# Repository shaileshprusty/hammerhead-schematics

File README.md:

# hammerhead-schematics
This is the official repository for the Circuit schematics of Hammer-Head (Autonomous Underwater Vehicle of NITR).

### Prerequisites
- [Autodesk Eagle](https://www.autodesk.com/products/eagle/overview)

#### Note
This repository is still under development

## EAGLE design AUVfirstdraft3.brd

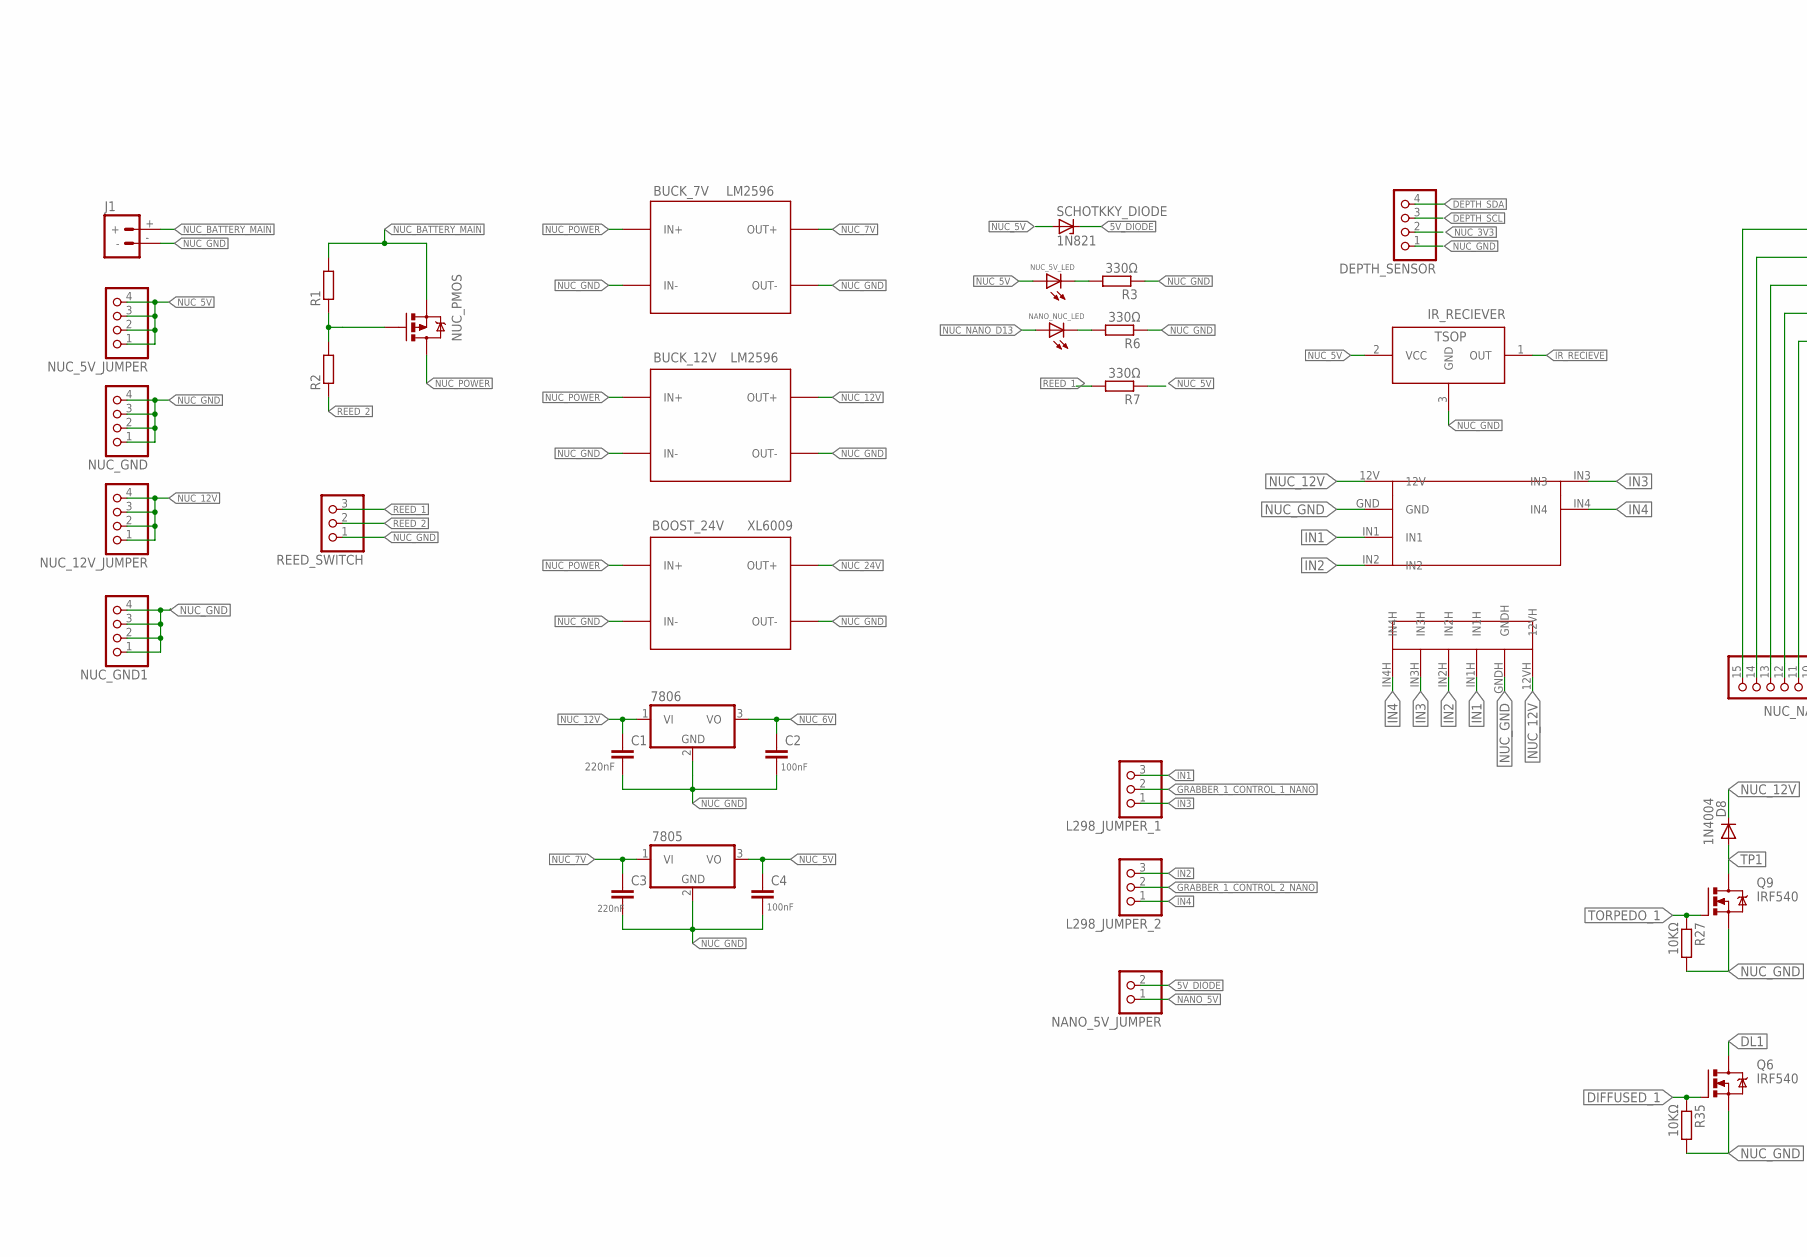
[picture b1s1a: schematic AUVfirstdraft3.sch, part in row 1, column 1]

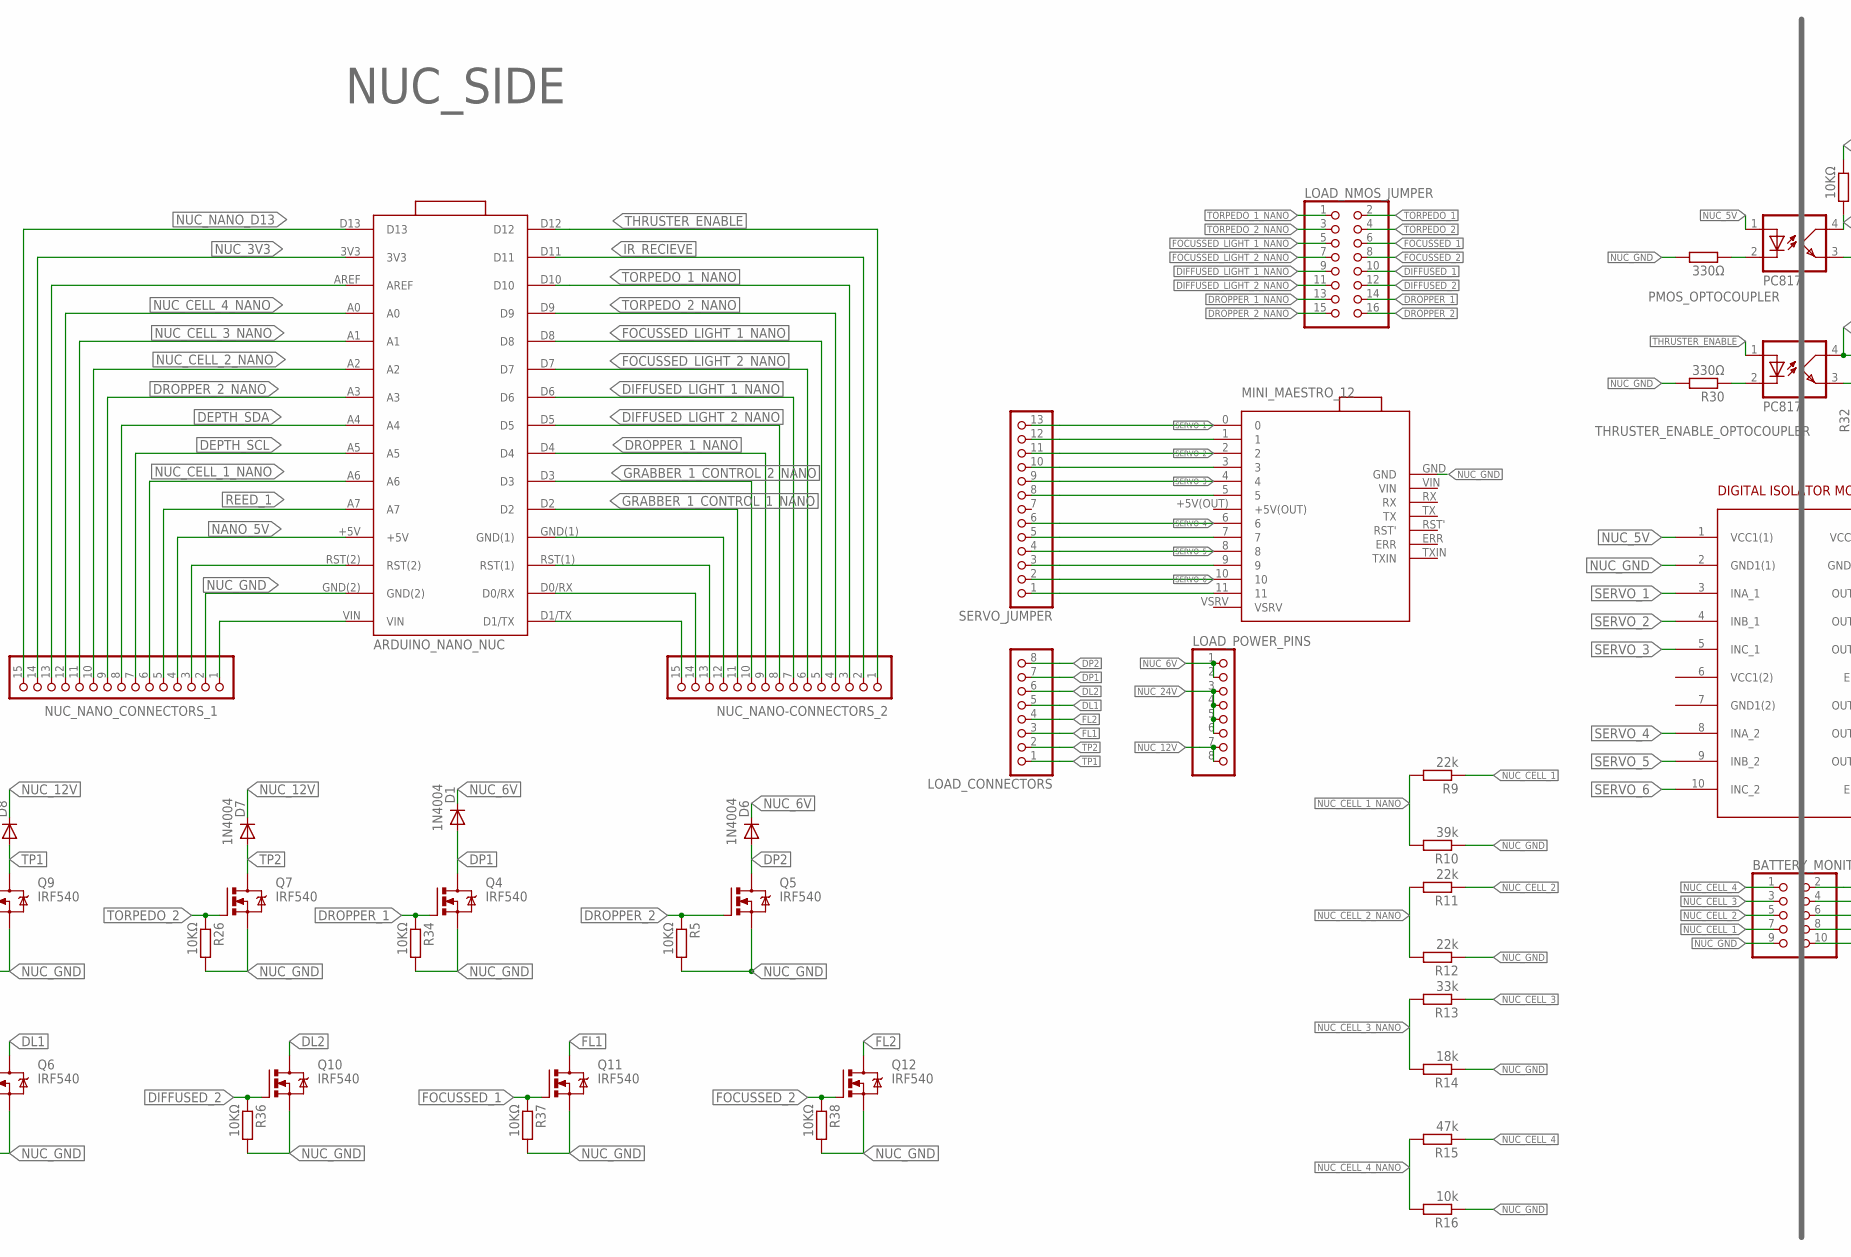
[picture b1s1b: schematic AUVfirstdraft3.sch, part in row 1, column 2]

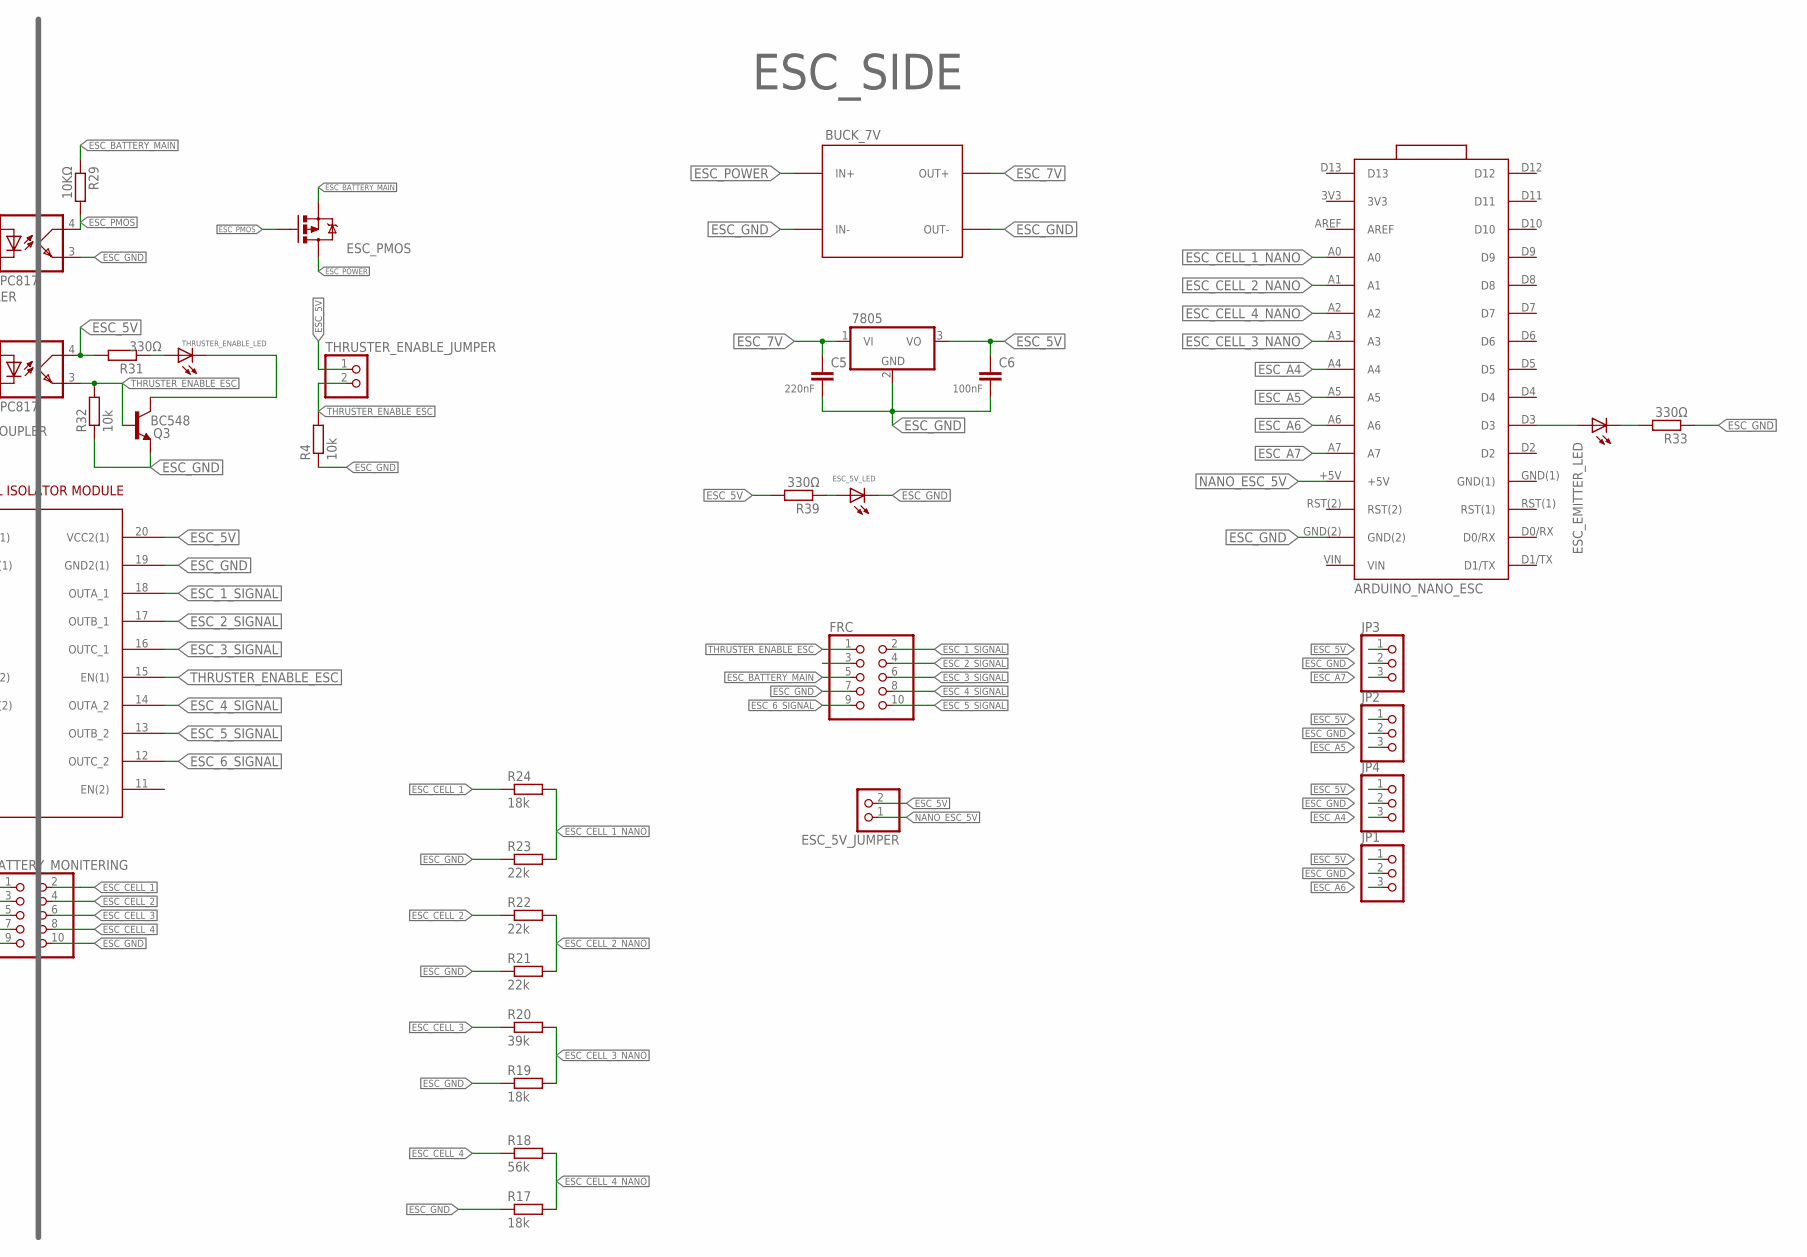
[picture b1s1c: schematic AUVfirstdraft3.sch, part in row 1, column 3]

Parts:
330Ω: R-EU_0204/7; 0204/7
7805_ESC, 7805_NUC, 7806_NUC: 7805TV; TO220V
BATTERY_MONITERING: PINHD-2X5; 2X05
BOOST_24V_NUC: DC-DC-STEP-DOWN-LM2596
BUCK_7V_ESC, BUCK_7V_NUC, BUCK_12_NUC: DC-DC-STEP-DOWN-LM2596
C1, C3, C5: 220nF; C025-024X044
C2, C4, C6: 100nF; C025-024X044
D1, D6, D7, D8: 1N4004; DO41-10
DEPTH_SENSOR: PINHD-1X4; 1X04
ESC_5V_JUMPER: PINHD-1X2; 1X02
ESC_5V_LED: LED3MM
ESC_EMITTER_LED: LED5MM
ESC_PMOS: MOSFET-PCHANNELFQP27P06; TO220V
FRC: PINHD-2X5; 2X05
IR_RECIEVER: TSOP34X; TSOP3XXX
ISOLATION_CIRCUIT: DIGITAL_ISOLATOR; DIGITAL_ISOLATOR_MODULE
J1: BATTERY_CONN_DEANS; DEANS
JP1, JP2, JP3, JP4: PINHD-1X3; 1X03
L298_JUMPER_1, L298_JUMPER_2: PINHD-1X3; 1X03
L298_MOTOR_DRIVER: L298MODULE
LOAD_CONNECTORS: PINHD-1X8; 1X08
LOAD_NMOS_JUMPER: PINHD-2X8; 2X08
LOAD_POWER_PINS: PINHD-1X8; 1X08
NANO_5V_JUMPER: PINHD-1X2; 1X02
NANO_NUC_LED: LED3MM
NUC_5V_JUMPER, NUC_12V_JUMPER: PINHD-1X4; 1X04
NUC_5V_LED: LED3MM
NUC_GND, NUC_GND1: PINHD-1X4; 1X04
NUC_NANO-CONNECTORS_2: PINHD-1X15; 1X15
NUC_NANO_CONNECTORS_1: PINHD-1X15; 1X15
NUC_PMOS: MOSFET-PCHANNELFQP27P06; TO220V
PMOS_OPTOCOUPLER: PC817; DIL04
Q3: BC548; TO92-EBC
Q4, Q5, Q6, Q7, Q9, Q10, Q11, Q12: IRF540; TO220BV
R1, R2: R-EU_0204/7; 0204/7
R3, R6, R7, R30, R31, R33, R39: 330Ω; 0204/7
R4, R16, R32: 10k; 0204/7
R5, R26, R27, R29, R34, R35, R36, R37, R38: 10KΩ; 0204/7
R9, R11, R12, R21, R22, R23: 22k; 0204/7
R10, R20: 39k; 0204/7
R13: 33k; 0204/7
R14, R17, R19, R24: 18k; 0204/7
R15: 47k; 0204/7
R18: 56k; 0204/7
REED_SWITCH: PINHD-1X3; 1X03
SCHOTKKY_DIODE: 1N821; DO35Z10
SERVO_JUMPER: PINHD-1X13; 1X13
THRUSTER_ENABLE_JUMPER: PINHD-1X2; 1X02
THRUSTER_ENABLE_LED: LED3MM
THRUSTER_ENABLE_OPTOCOUPLER: PC817; DIL04
U$1, U$6: ARDUINO(NANO_3.0); ARDUINO_NANO_30PIN
U$4: SERVO_CONTROLLER

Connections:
5V_DIODE: NANO_5V_JUMPER.2, SCHOTKKY_DIODE.C
DEPTH_SCL: DEPTH_SENSOR.3, NUC_NANO_CONNECTORS_1.7, U$1.A5
DEPTH_SDA: DEPTH_SENSOR.4, NUC_NANO_CONNECTORS_1.8, U$1.A4
DIFFUSED_1: LOAD_NMOS_JUMPER.10, Q6.G, R35.1
DIFFUSED_2: LOAD_NMOS_JUMPER.12, Q10.G, R36.1
DIFFUSED_LIGHT_1_NANO: LOAD_NMOS_JUMPER.9, NUC_NANO-CONNECTORS_2.7, U$1.D6
DIFFUSED_LIGHT_2_NANO: LOAD_NMOS_JUMPER.11, NUC_NANO-CONNECTORS_2.8, U$1.D5
DL1: LOAD_CONNECTORS.5, Q6.D
DL2: LOAD_CONNECTORS.6, Q10.D
DP1: D1.A, LOAD_CONNECTORS.7, Q4.D
DP2: D6.A, LOAD_CONNECTORS.8, Q5.D
DROPPER_1: LOAD_NMOS_JUMPER.14, Q4.G, R34.1
DROPPER_1_NANO: LOAD_NMOS_JUMPER.13, NUC_NANO-CONNECTORS_2.9, U$1.D4
DROPPER_2: LOAD_NMOS_JUMPER.16, Q5.G, R5.1
DROPPER_2_NANO: LOAD_NMOS_JUMPER.15, NUC_NANO_CONNECTORS_1.9, U$1.A3
ESC_1_SIGNAL: FRC.2, ISOLATION_CIRCUIT.18 (OUTA_1)
ESC_2_SIGNAL: FRC.4, ISOLATION_CIRCUIT.17 (OUTB_1)
ESC_3_SIGNAL: FRC.6, ISOLATION_CIRCUIT.16 (OUTC_1)
ESC_4_SIGNAL: FRC.8, ISOLATION_CIRCUIT.14 (OUTA_2)
ESC_5V: 7805_ESC.3 (VO), C6.1, ESC_5V_JUMPER.2, ISOLATION_CIRCUIT.20 (VCC2(1)), JP1.1, JP2.1, JP3.1, JP4.1, R31.2, R39.2, THRUSTER_ENABLE_JUMPER.1, THRUSTER_ENABLE_OPTOCOUPLER.4 (COL)
ESC_5_SIGNAL: FRC.10, ISOLATION_CIRCUIT.13 (OUTB_2)
ESC_6_SIGNAL: FRC.9, ISOLATION_CIRCUIT.12 (OUTC_2)
ESC_7V: 7805_ESC.1 (VI), BUCK_7V_ESC.OUT+, C5.1
ESC_A4: JP4.3, U$6.A4
ESC_A5: JP2.3, U$6.A5
ESC_A6: JP1.3, U$6.A6
ESC_A7: JP3.3, U$6.A7
ESC_BATTERY_MAIN: ESC_PMOS.3 (S), FRC.5, R29.1
ESC_CELL_1: BATTERY_MONITERING.2, R24.1
ESC_CELL_1_NANO: R23.2, R24.2, U$6.A0
ESC_CELL_2: BATTERY_MONITERING.4, R22.1
ESC_CELL_2_NANO: R21.2, R22.2, U$6.A1
ESC_CELL_3: BATTERY_MONITERING.6, R20.1
ESC_CELL_3_NANO: R19.2, R20.2, U$6.A3
ESC_CELL_4: BATTERY_MONITERING.8, R18.1
ESC_CELL_4_NANO: R17.2, R18.2, U$6.A2
ESC_GND: 7805_ESC.2 (GND), BATTERY_MONITERING.10, BUCK_7V_ESC.IN-, BUCK_7V_ESC.OUT-, C5.2, C6.2, ESC_5V_LED.K (C), FRC.7, ISOLATION_CIRCUIT.19 (GND2(1)), JP1.2, JP2.2, JP3.2, JP4.2, PMOS_OPTOCOUPLER.3 (EMIT), Q3.E, R4.1, R17.1, R19.1, R21.1, R23.1, R32.1, R33.1, U$6.GND(2)
ESC_PMOS: ESC_PMOS.1 (G), PMOS_OPTOCOUPLER.4 (COL), R29.2
ESC_POWER: BUCK_7V_ESC.IN+, ESC_PMOS.2 (D)
FL1: LOAD_CONNECTORS.3, Q11.D
FL2: LOAD_CONNECTORS.4, Q12.D
FOCUSSED_1: LOAD_NMOS_JUMPER.6, Q11.G, R37.1
FOCUSSED_2: LOAD_NMOS_JUMPER.8, Q12.G, R38.1
FOCUSSED_LIGHT_1_NANO: LOAD_NMOS_JUMPER.5, NUC_NANO-CONNECTORS_2.5, U$1.D8
FOCUSSED_LIGHT_2_NANO: LOAD_NMOS_JUMPER.7, NUC_NANO-CONNECTORS_2.6, U$1.D7
GRABBER_1_CONTROL_1_NANO: L298_JUMPER_1.2, NUC_NANO-CONNECTORS_2.11, U$1.D2
GRABBER_1_CONTROL_2_NANO: L298_JUMPER_2.2, NUC_NANO-CONNECTORS_2.10, U$1.D3
IN1: L298_JUMPER_1.3, L298_MOTOR_DRIVER.IN1, L298_MOTOR_DRIVER.IN1H
IN2: L298_JUMPER_2.3, L298_MOTOR_DRIVER.IN2, L298_MOTOR_DRIVER.IN2H
IN3: L298_JUMPER_1.1, L298_MOTOR_DRIVER.IN3, L298_MOTOR_DRIVER.IN3H
IN4: L298_JUMPER_2.1, L298_MOTOR_DRIVER.IN4, L298_MOTOR_DRIVER.IN4H
IR_RECIEVE: IR_RECIEVER.1 (OUT), NUC_NANO-CONNECTORS_2.2, U$1.D11
unnamed: NUC_NANO_CONNECTORS_1.1, U$1.VIN
unnamed: NANO_NUC_LED.K (C), R6.2
unnamed: R31.1, THRUSTER_ENABLE_LED.A
unnamed: ESC_5V_LED.A, R39.1
unnamed: SERVO_JUMPER.12, U$4.1
unnamed: NUC_NANO_CONNECTORS_1.3, U$1.RST(2)
unnamed: 330Ω.1, PMOS_OPTOCOUPLER.2 (C)
unnamed: SERVO_JUMPER.10, U$4.3
unnamed: ESC_EMITTER_LED.A, U$6.D3
unnamed: SERVO_JUMPER.8, U$4.5
unnamed: SERVO_JUMPER.5, U$4.7
unnamed: R30.1, THRUSTER_ENABLE_OPTOCOUPLER.2 (C)
unnamed: SERVO_JUMPER.3, U$4.9
unnamed: Q3.C, THRUSTER_ENABLE_LED.K (C)
unnamed: NUC_NANO_CONNECTORS_1.13, U$1.AREF
unnamed: ESC_EMITTER_LED.K (C), R33.2
unnamed: SERVO_JUMPER.1, U$4.11
unnamed: NUC_NANO-CONNECTORS_2.15, U$1.D1/TX
unnamed: NUC_NANO-CONNECTORS_2.14, U$1.D0/RX
unnamed: NUC_NANO-CONNECTORS_2.13, U$1.RST(1)
unnamed: NUC_NANO-CONNECTORS_2.12, U$1.GND(1)
unnamed: NUC_PMOS.1 (G), R1.1, R2.2
unnamed: NUC_5V_LED.K (C), R3.2
NANO_5V: NANO_5V_JUMPER.1, NUC_NANO_CONNECTORS_1.4, U$1.+5V
NANO_ESC_5V: ESC_5V_JUMPER.1, U$6.+5V
NUC_3V3: DEPTH_SENSOR.2, NUC_NANO_CONNECTORS_1.14, U$1.3V3
NUC_5V: 7805_NUC.3 (VO), C4.1, IR_RECIEVER.2 (VCC), ISOLATION_CIRCUIT.1 (VCC1(1)), NUC_5V_JUMPER.1, NUC_5V_JUMPER.2, NUC_5V_JUMPER.3, NUC_5V_JUMPER.4, NUC_5V_LED.A, PMOS_OPTOCOUPLER.1 (A), R7.1, SCHOTKKY_DIODE.A
NUC_6V: 7806_NUC.3 (VO), C2.1, D1.C, D6.C, LOAD_POWER_PINS.1, LOAD_POWER_PINS.2
NUC_7V: 7805_NUC.1 (VI), BUCK_7V_NUC.OUT+, C3.1
NUC_12V: 7806_NUC.1 (VI), BUCK_12_NUC.OUT+, C1.1, D7.C, D8.C, L298_MOTOR_DRIVER.12V, L298_MOTOR_DRIVER.12VH, LOAD_POWER_PINS.7, LOAD_POWER_PINS.8, NUC_12V_JUMPER.1, NUC_12V_JUMPER.2, NUC_12V_JUMPER.3, NUC_12V_JUMPER.4
NUC_24V: BOOST_24V_NUC.OUT+, LOAD_POWER_PINS.3, LOAD_POWER_PINS.4, LOAD_POWER_PINS.5, LOAD_POWER_PINS.6
NUC_BATTERY_MAIN: J1.+, NUC_PMOS.3 (S), R1.2
NUC_CELL_1: BATTERY_MONITERING.7, R9.1
NUC_CELL_1_NANO: NUC_NANO_CONNECTORS_1.6, R9.2, R10.2, U$1.A6
NUC_CELL_2: BATTERY_MONITERING.5, R11.1
NUC_CELL_2_NANO: NUC_NANO_CONNECTORS_1.10, R11.2, R12.2, U$1.A2
NUC_CELL_3: BATTERY_MONITERING.3, R13.1
NUC_CELL_3_NANO: NUC_NANO_CONNECTORS_1.11, R13.2, R14.2, U$1.A1
NUC_CELL_4: BATTERY_MONITERING.1, R15.1
NUC_CELL_4_NANO: NUC_NANO_CONNECTORS_1.12, R15.2, R16.2, U$1.A0
NUC_GND: 330Ω.2, 7805_NUC.2 (GND), 7806_NUC.2 (GND), BATTERY_MONITERING.9, BOOST_24V_NUC.IN-, BOOST_24V_NUC.OUT-, BUCK_7V_NUC.IN-, BUCK_7V_NUC.OUT-, BUCK_12_NUC.IN-, BUCK_12_NUC.OUT-, C1.2, C2.2, C3.2, C4.2, DEPTH_SENSOR.1, IR_RECIEVER.3 (GND), ISOLATION_CIRCUIT.2 (GND1(1)), J1.-, L298_MOTOR_DRIVER.GND, L298_MOTOR_DRIVER.GNDH, NUC_GND.1, NUC_GND.2, NUC_GND.3, NUC_GND.4, NUC_GND1.1, NUC_GND1.2, NUC_GND1.3, NUC_GND1.4, NUC_NANO_CONNECTORS_1.2, Q4.S, Q5.S, Q6.S, Q7.S, Q9.S, Q10.S, Q11.S, Q12.S, R3.1, R5.2, R6.1, R10.1, R12.1, R14.1, R16.1, R26.2, R27.2, R30.2, R34.2, R35.2, R36.2, R37.2, R38.2, REED_SWITCH.1, U$1.GND(2), U$4.GND
NUC_NANO_D13: NANO_NUC_LED.A, NUC_NANO_CONNECTORS_1.15, U$1.D13
NUC_POWER: BOOST_24V_NUC.IN+, BUCK_7V_NUC.IN+, BUCK_12_NUC.IN+, NUC_PMOS.2 (D)
REED_1: NUC_NANO_CONNECTORS_1.5, R7.2, REED_SWITCH.3, U$1.A7
REED_2: R2.1, REED_SWITCH.2
SERVO_1: ISOLATION_CIRCUIT.3 (INA_1), SERVO_JUMPER.13, U$4.0
SERVO_2: ISOLATION_CIRCUIT.4 (INB_1), SERVO_JUMPER.11, U$4.2
SERVO_3: ISOLATION_CIRCUIT.5 (INC_1), SERVO_JUMPER.9, U$4.4
SERVO_4: ISOLATION_CIRCUIT.8 (INA_2), SERVO_JUMPER.6, U$4.6
SERVO_5: ISOLATION_CIRCUIT.9 (INB_2), SERVO_JUMPER.4, U$4.8
SERVO_6: ISOLATION_CIRCUIT.10 (INC_2), SERVO_JUMPER.2, U$4.10
THRUSTER_ENABLE: NUC_NANO-CONNECTORS_2.1, THRUSTER_ENABLE_OPTOCOUPLER.1 (A), U$1.D12
THRUSTER_ENABLE_ESC: FRC.1, ISOLATION_CIRCUIT.15 (EN(1)), Q3.B, R4.2, R32.2, THRUSTER_ENABLE_JUMPER.2, THRUSTER_ENABLE_OPTOCOUPLER.3 (EMIT)
TORPEDO_1: LOAD_NMOS_JUMPER.2, Q9.G, R27.1
TORPEDO_1_NANO: LOAD_NMOS_JUMPER.1, NUC_NANO-CONNECTORS_2.3, U$1.D10
TORPEDO_2: LOAD_NMOS_JUMPER.4, Q7.G, R26.1
TORPEDO_2_NANO: LOAD_NMOS_JUMPER.3, NUC_NANO-CONNECTORS_2.4, U$1.D9
TP1: D8.A, LOAD_CONNECTORS.1, Q9.D
TP2: D7.A, LOAD_CONNECTORS.2, Q7.D

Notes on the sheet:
BUCK_7V
BUCK_12V
BOOST_24V
7805
7806
NUC_SIDE
ESC_SIDE
MINI_MAESTRO_12
ARDUINO_NANO_NUC
ARDUINO_NANO_ESC
LM2596
XL6009

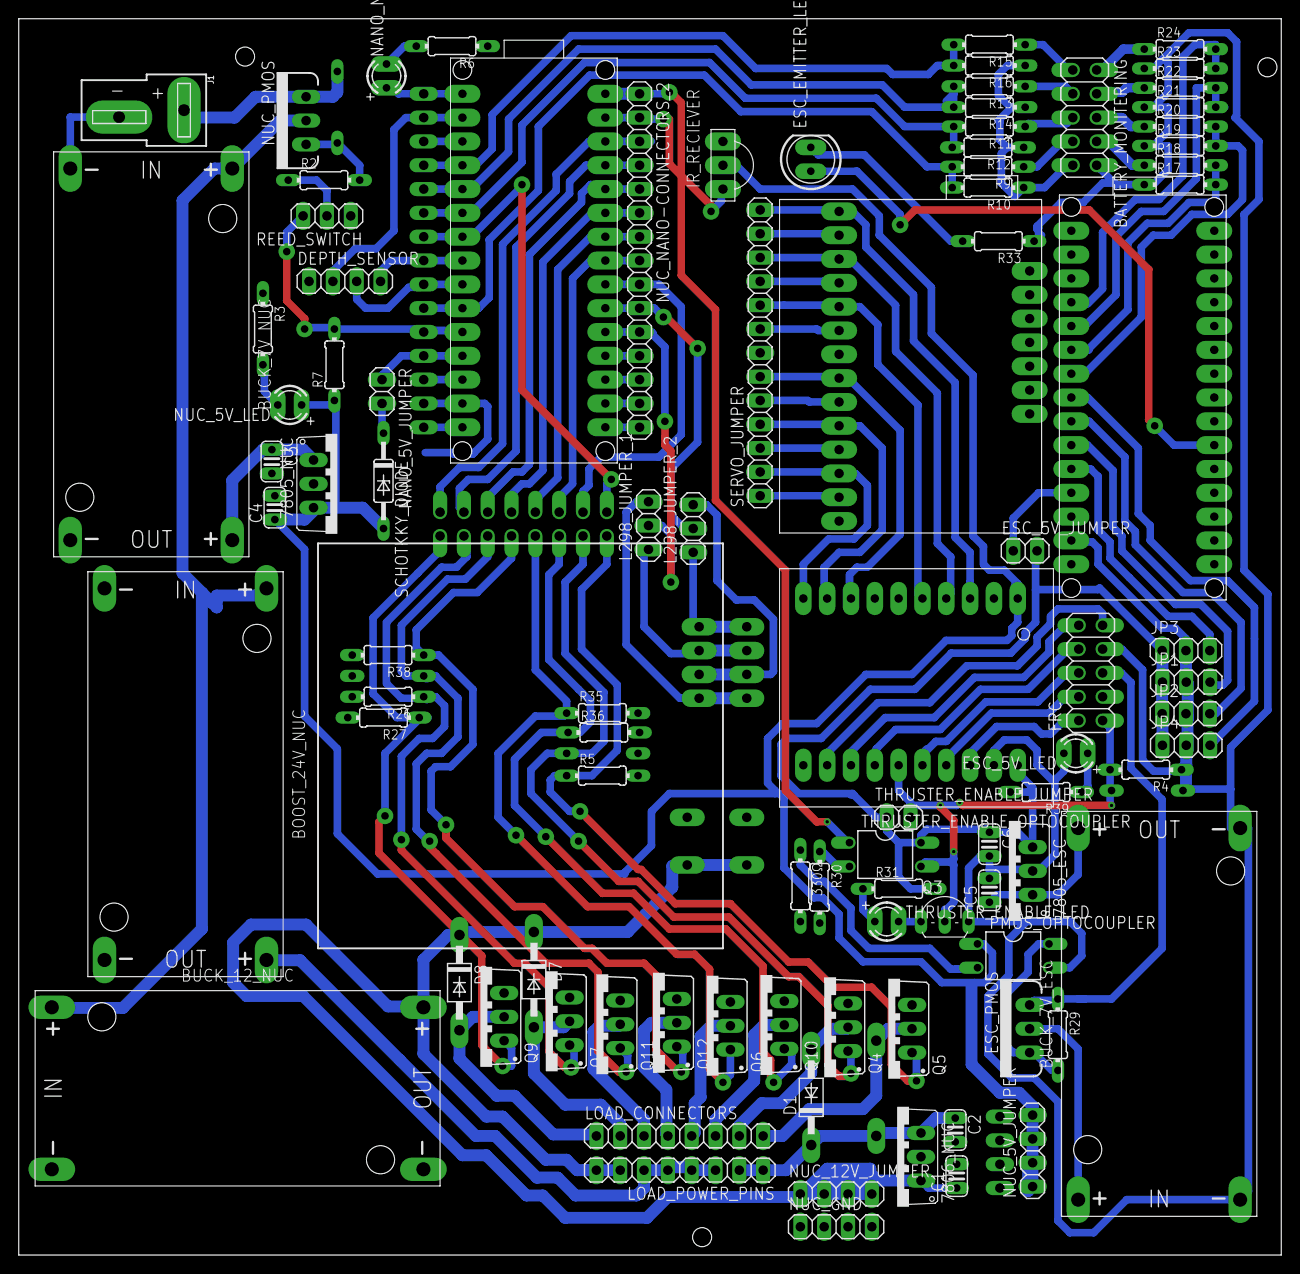
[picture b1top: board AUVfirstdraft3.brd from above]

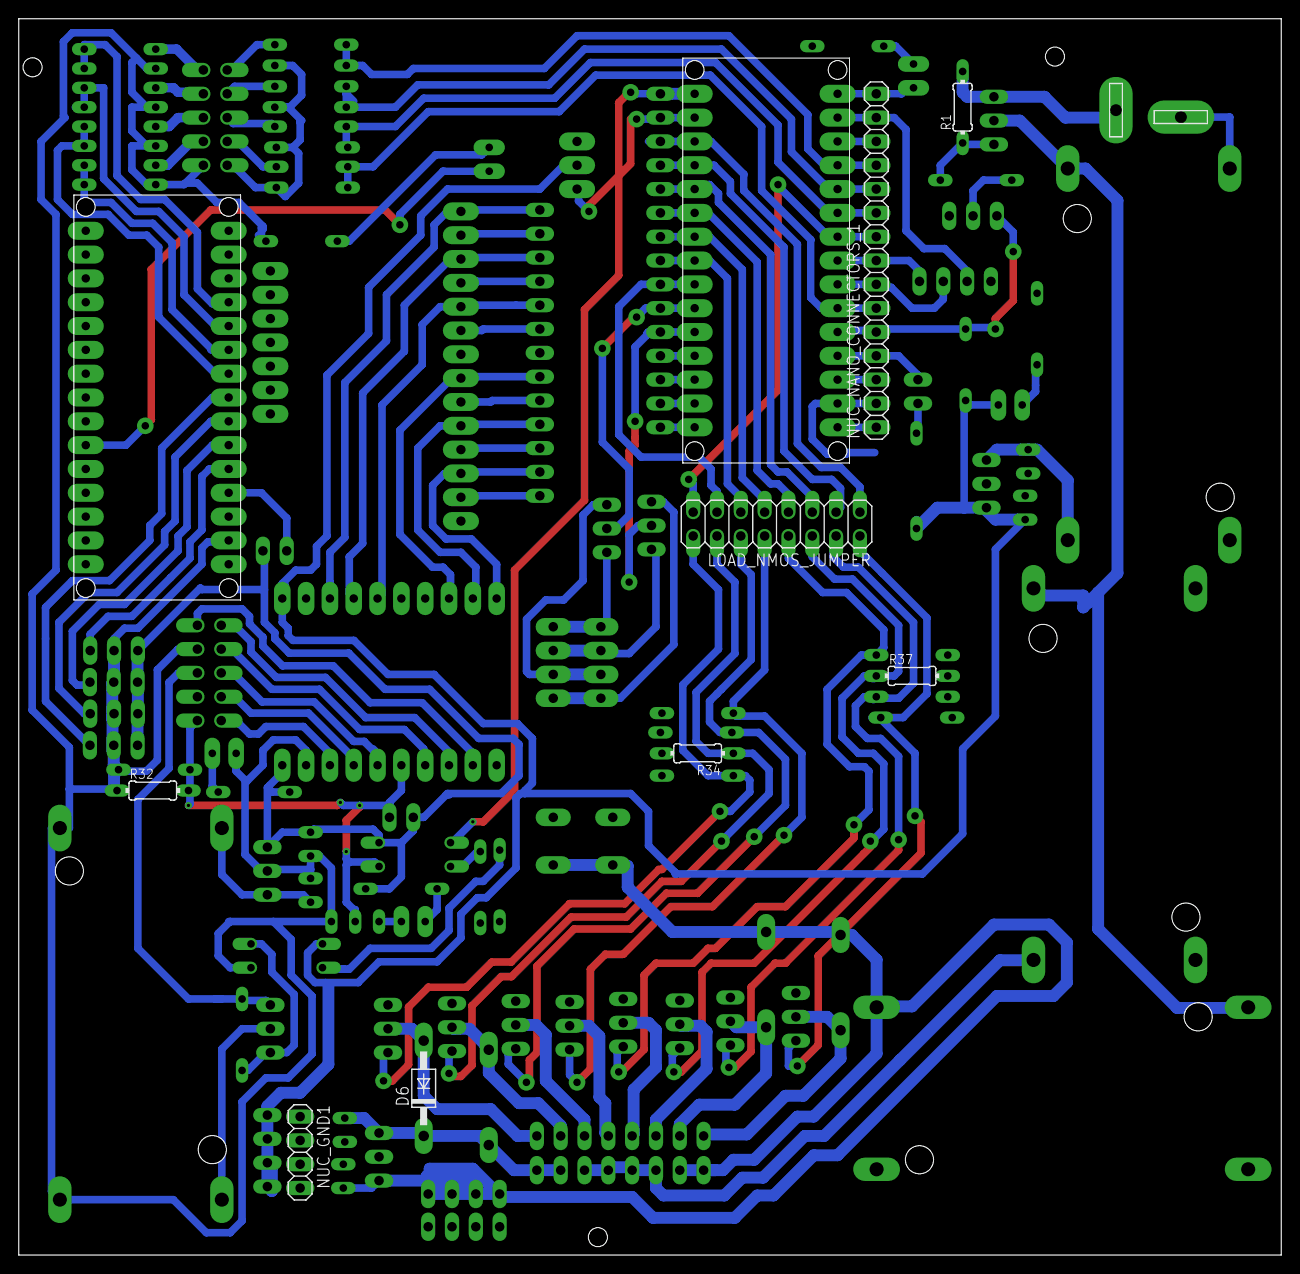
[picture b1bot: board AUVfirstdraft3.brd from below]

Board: 2 copper layers, 134.5 x 131.7 mm, 103 parts (8 on the bottom side), 111 nets.

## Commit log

2018-10-23 Final Design
2018-10-23 Modify ReadME
2018-10-23 Create License file

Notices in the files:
parts and their libraries:
diy-modules: Released under the Creative Commons Attribution 4.0 International License: http://creativecommons.org/licenses/by/4.0
